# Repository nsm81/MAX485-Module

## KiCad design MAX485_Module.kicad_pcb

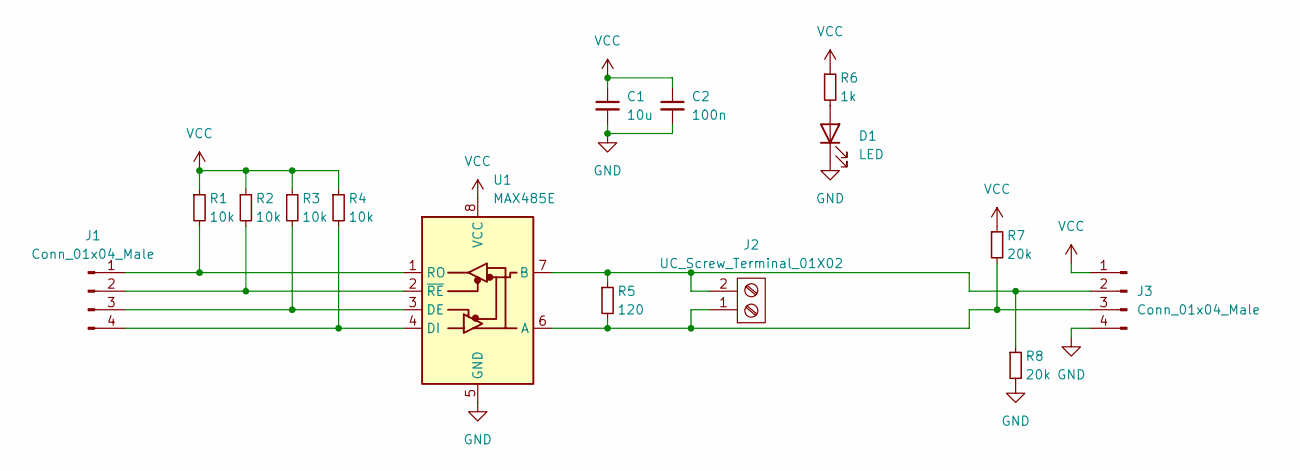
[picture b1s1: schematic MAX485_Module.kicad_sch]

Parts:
C1: 10u; C_1206_3216Metric
C2: 100n; C_1206_3216Metric
D1: LED; LED_1206_3216Metric
J1, J3: Conn_01x04_Male; PinHeader_1x04_P2.54mm_Vertical
J2: UC_Screw_Terminal_01X02; TerminalBlock_Phoenix_MKDS-1,5-2-5.08_1x02_P5.08mm_Horizont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
R1, R2, R3, R4: 10k; R_1206_3216Metric
R5: 120; R_1206_3216Metric
R6: 1k; R_1206_3216Metric
R7, R8: 20k; R_1206_3216Metric
U1: MAX485E; SOIC-8_3.9x4.9mm_P1.27mm

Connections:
GND: C1.2, C2.2, D1.1 (K), J3.4, R8.2, U1.5 (GND)
unnamed: D1.2 (A), R6.2
unnamed: J1.1, R1.2, U1.1 (RO)
unnamed: J1.2, R2.2, U1.2 (~RE)
unnamed: J1.3, R3.2, U1.3 (DE)
unnamed: J1.4, R4.2, U1.4 (DI)
unnamed: J2.1, J3.3, R5.2, R7.2, U1.6 (A)
unnamed: J2.2, J3.2, R5.1, R8.1, U1.7 (B)
VCC: C1.1, C2.1, J3.1, R1.1, R2.1, R3.1, R4.1, R6.1, R7.1, U1.8 (VCC)

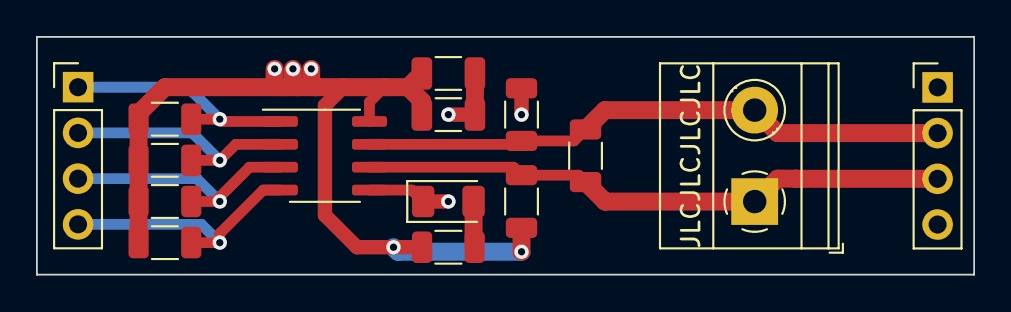
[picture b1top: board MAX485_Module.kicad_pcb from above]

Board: 2 copper layers, 52.1 x 13.2 mm, 15 parts (0 on the bottom side), 9 nets.

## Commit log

2022-03-17 Initial Commit completed PCB
